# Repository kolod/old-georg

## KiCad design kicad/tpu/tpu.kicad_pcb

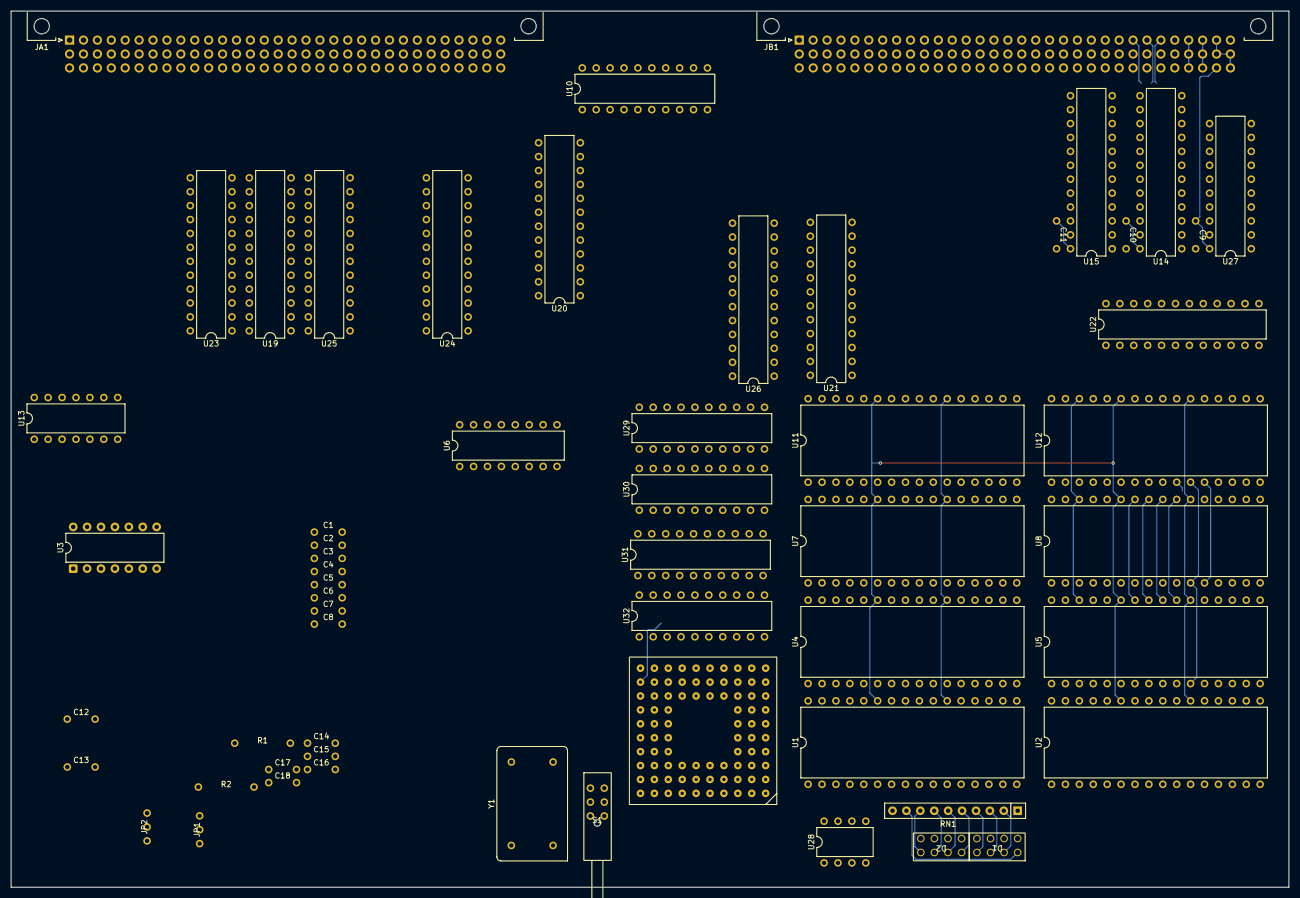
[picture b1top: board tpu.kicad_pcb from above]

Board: 4 copper layers, 233.4 x 160.0 mm, 58 parts (0 on the bottom side), 184 nets.

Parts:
C1, C2, C3, C4, C5, C6, C7, C8, C9, C10, C11, C12, C13, C14, C15, C16, C17, C18: 100nF; C104
D1, D2: 555-4001
JA1: 0903196X921
JB1: 0903196X921
JP1, JP2: Jumper
R1, R2: 100; R101
RN1: 1k; R_Array_SIP10
S1: 1840.6131
U1, U2, U4, U5, U7, U8, U11, U12: V62C5181024LL-70P; DIP-32_W15.24mm-tight
U3: 74F32; DIP-14_W7.62mm
U6: 74LS123; DIP-16_W7.62mm-tight
U10: 74F240; DIP-20_W7.62mm-tight
U13: 74S37; DIP-14_W7.62mm-tight
U14, U15: 74F842; DIP-24_W7.62mm-tight
U16: 84pin grid array
U19, U20, U21, U22, U23, U24, U25, U26: PALCE20V8H-15PC/4; DIP-24_W7.62mm-tight
U27: 74F640; DIP-20_W7.62mm-tight
U28: MAX690xPA; DIP-8_W7.62mm-tight
U29, U30, U31, U32: 74F573; DIP-20_W7.62mm-tight
Y1: IQXO-350C; Oscillator_DIP-14-tight

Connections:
+5V: C1.1, C2.1, C3.1, C4.1, C5.1, C6.1, C7.1, C8.1, C9.1, C10.1, C11.1, C12.1, C13.1, C14.1, C15.1, C16.1, JA1.a1, JA1.a2, JA1.b1, JA1.b2, JA1.c1, JA1.c2, JB1.a31, JB1.a32, JB1.b31, JB1.b32, JB1.c31, JB1.c32, JP1.3 (B), RN1.1 (R1), U1.30 (CS2/CE2), U1.32 (VCC), U2.30 (CS2/CE2), U2.32 (VCC), U3.14 (VCC), U4.30 (CS2/CE2), U4.32 (VCC), U5.30 (CS2/CE2), U5.32 (VCC), U6.9 (A), U6.16 (VCC), U7.30 (CS2/CE2), U7.32 (VCC), U8.30 (CS2/CE2), U8.32 (VCC), U10.20 (VCC), U11.30 (CS2/CE2), U11.32 (VCC), U12.30 (CS2/CE2), U12.32 (VCC), U13.1, U13.4, U13.14 (VCC), U14.24 (VCC), U15.24 (VCC), U16.A2 (Link_Special), U16.C2 (VDD), U16.C5 (VDD), U16.E2 (Boot_from_ROM), U16.E10 (VDD), U16.H4 (VDD), U19.24 (VCC), U20.24 (VCC), U21.24 (VCC), U22.24 (VCC), U23.24 (VCC), U24.24 (VCC), U25.24 (VCC), U26.24 (VCC), U27.20 (VCC), U28.2 (VCC), U29.20 (VCC), U30.20 (VCC), U31.20 (VCC), U32.20 (VCC), Y1.14 (Vcc)
/Multibus/ADR0: JB1.a24, U15.23 (Q0)
/Multibus/ADR1: JB1.b24, U15.22 (Q1)
/Multibus/ADR2: JB1.a23, U15.21 (Q2)
/Multibus/ADR3: JB1.b23, U15.20 (Q3)
/Multibus/ADR4: JB1.a22, U15.19 (Q4)
/Multibus/ADR5: JB1.b22, U15.18 (Q5)
/Multibus/ADR6: JB1.a21, U15.17 (Q6)
/Multibus/ADR7: JB1.b21, U15.16 (Q7)
/Multibus/ADR8: JB1.a20, U15.15 (Q8)
/Multibus/ADR9: JB1.b20, U15.14 (Q9)
/Multibus/ADR10: JB1.a19, U14.23 (Q0)
/Multibus/ADR11: JB1.b19, U14.22 (Q1)
/Multibus/ADR12: JB1.a18, U14.21 (Q2)
/Multibus/ADR13: JB1.b18, U14.20 (Q3)
/Multibus/ADR14: JB1.a17, U14.19 (Q4)
/Multibus/ADR15: JB1.b17, U14.18 (Q5)
/Multibus/ADR16: JB1.a16, U14.17 (Q6)
/Multibus/ADR17: JB1.b16, U14.16 (Q7)
/Multibus/ADR18: JB1.a15, U14.15 (Q8)
/Multibus/ADR19: JB1.b15, U14.14 (Q9)
/Multibus/DAT0: JB1.a28, U27.18 (B0)
/Multibus/DAT1: JB1.b28, U27.17 (B1)
/Multibus/DAT2: JB1.a27, U27.16 (B2)
/Multibus/DAT3: JB1.b27 (b26), U27.15 (B3)
/Multibus/DAT4: JB1.a26, U27.14 (B4)
/Multibus/DAT5: JB1.b26, U27.13 (B5)
/Multibus/DAT6: JB1.a25, U27.12 (B6)
/Multibus/DAT7: JB1.b25, U27.11 (B7)
/RAM/D0: U1.13 (I/O0), U2.13 (I/O0)
/RAM/D1: U1.14 (I/O1), U2.14 (I/O1)
/RAM/D2: U1.15 (I/O2), U2.15 (I/O2)
/RAM/D3: U1.17 (I/O3), U2.17 (I/O3)
/RAM/D4: U1.18 (I/O4), U2.18 (I/O4)
/RAM/D5: U1.19 (I/O5), U2.19 (I/O5)
/RAM/D6: U1.20 (I/O6), U2.20 (I/O6)
/RAM/D7: U1.21 (I/O7), U2.21 (I/O7)
/RAM/D8: U4.13 (I/O0), U5.13 (I/O0)
/RAM/D9: U4.14 (I/O1), U5.14 (I/O1)
/RAM/D10: U4.15 (I/O2), U5.15 (I/O2)
/RAM/D11: U4.17 (I/O3), U5.17 (I/O3)
/RAM/D12: U4.18 (I/O4), U5.18 (I/O4)
/RAM/D13: U4.19 (I/O5), U5.19 (I/O5)
/RAM/D14: U4.20 (I/O6), U5.20 (I/O6)
/RAM/D15: U4.21 (I/O7), U5.21 (I/O7)
/RAM/D16: U7.13 (I/O0), U8.13 (I/O0)
/RAM/D17: U7.14 (I/O1), U8.14 (I/O1)
/RAM/D18: U7.15 (I/O2), U8.15 (I/O2)
/RAM/D19: U7.17 (I/O3), U8.17 (I/O3)
/RAM/D20: U7.18 (I/O4), U8.18 (I/O4)
/RAM/D21: U7.19 (I/O5), U8.19 (I/O5)
/RAM/D22: U7.20 (I/O6), U8.20 (I/O6)
/RAM/D23: U7.21 (I/O7), U8.21 (I/O7)
/RAM/D24: U11.13 (I/O0), U12.13 (I/O0)
/RAM/D25: U11.14 (I/O1), U12.14 (I/O1)
/RAM/D26: U11.15 (I/O2), U12.15 (I/O2)
/RAM/D27: U11.17 (I/O3), U12.17 (I/O3)
/RAM/D28: U11.18 (I/O4), U12.18 (I/O4)
/RAM/D29: U11.19 (I/O5), U12.19 (I/O5)
/RAM/D30: U11.20 (I/O6), U12.20 (I/O6)
/RAM/D31: U11.21 (I/O7), U12.21 (I/O7)
/RAM_SIZE: JP1.2 (C), U23.18 (I/O3)
/~RESET: S1.2, U28.7 (~RESET)
A0: U1.12 (A0), U2.12 (A0), U4.12 (A0), U5.12 (A0), U7.12 (A0), U8.12 (A0), U11.12 (A0), U12.12 (A0), U15.2 (D0), U19.2 (I1), U29.19 (Q0)
A1: U1.11 (A1), U2.11 (A1), U4.11 (A1), U5.11 (A1), U7.11 (A1), U8.11 (A1), U11.11 (A1), U12.11 (A1), U15.3 (D1), U19.3 (I2), U29.18 (Q1)
A2: U1.10 (A2), U2.10 (A2), U4.10 (A2), U5.10 (A2), U7.10 (A2), U8.10 (A2), U11.10 (A2), U12.10 (A2), U15.4 (D2), U19.4 (I3), U29.17 (Q2)
A3: U1.9 (A3), U2.9 (A3), U4.9 (A3), U5.9 (A3), U7.9 (A3), U8.9 (A3), U11.9 (A3), U12.9 (A3), U15.5 (D3), U19.23 (I13), U29.16 (Q3)
A4: U1.8 (A4), U2.8 (A4), U4.8 (A4), U5.8 (A4), U7.8 (A4), U8.8 (A4), U11.8 (A4), U12.8 (A4), U15.6 (D4), U29.15 (Q4)
A5: U1.7 (A5), U2.7 (A5), U4.7 (A5), U5.7 (A5), U7.7 (A5), U8.7 (A5), U11.7 (A5), U12.7 (A5), U15.7 (D5), U29.14 (Q5)
A6: U1.6 (A6), U2.6 (A6), U4.6 (A6), U5.6 (A6), U7.6 (A6), U8.6 (A6), U11.6 (A6), U12.6 (A6), U15.8 (D6), U29.13 (Q6)
A7: U1.5 (A7), U2.5 (A7), U4.5 (A7), U5.5 (A7), U7.5 (A7), U8.5 (A7), U11.5 (A7), U12.5 (A7), U15.9 (D7), U29.12 (Q7)
A8: U1.27 (A8), U2.27 (A8), U4.27 (A8), U5.27 (A8), U7.27 (A8), U8.27 (A8), U11.27 (A8), U12.27 (A8), U15.10 (D8), U30.12 (Q7)
A9: U1.26 (A9), U2.26 (A9), U4.26 (A9), U5.26 (A9), U7.26 (A9), U8.26 (A9), U11.26 (A9), U12.26 (A9), U15.11 (D9), U30.13 (Q6)
A10: U1.23 (A10), U2.23 (A10), U4.23 (A10), U5.23 (A10), U7.23 (A10), U8.23 (A10), U11.23 (A10), U12.23 (A10), U14.2 (D0), U30.14 (Q5)
A11: U1.25 (A11), U2.25 (A11), U4.25 (A11), U5.25 (A11), U7.25 (A11), U8.25 (A11), U11.25 (A11), U12.25 (A11), U14.3 (D1), U30.15 (Q4)
A12: U1.4 (A12), U2.4 (A12), U4.4 (A12), U5.4 (A12), U7.4 (A12), U8.4 (A12), U11.4 (A12), U12.4 (A12), U14.4 (D2), U30.16 (Q3)
A13: U1.28 (A13), U2.28 (A13), U4.28 (A13), U5.28 (A13), U7.28 (A13), U8.28 (A13), U11.28 (A13), U12.28 (A13), U14.5 (D3), U30.17 (Q2)
A14: U1.3 (A14), U2.3 (A14), U4.3 (A14), U5.3 (A14), U7.3 (A14), U8.3 (A14), U11.3 (A14), U12.3 (A14), U14.6 (D4), U30.18 (Q1)
A15: U1.31 (A15), U2.31 (A15), U4.31 (A15), U5.31 (A15), U7.31 (A15), U8.31 (A15), U11.31 (A15), U12.31 (A15), U14.7 (D5), U30.19 (Q0)
A16: U1.2 (A16), U2.2 (A16), U4.2 (A16), U5.2 (A16), U7.2 (A16), U8.2 (A16), U11.2 (A16), U12.2 (A16), U14.8 (D6), U31.19 (Q0)
A17: U14.9 (D7), U31.18 (Q1)
A18: U14.10 (D8), U31.17 (Q2)
A19: U14.11 (D9), U31.16 (Q3)
AD2: U16.J10 (AD2), U27.4 (A2), U29.2 (D0)
AD3: U16.H9 (AD3), U27.5 (A3), U29.3 (D1)
AD4: U16.H8 (AD4), U27.6 (A4), U29.4 (D2)
AD5: U16.J9 (AD5), U27.7 (A5), U29.5 (D3)
AD6: U16.J8 (AD6), U27.8 (A6), U29.6 (D4)
AD7: U16.K10 (AD7), U27.9 (A7), U29.7 (D5)
AD8: U16.H7 (AD8), U29.8 (D6)
AD9: U16.K9 (AD9), U29.9 (D7)
AD10: U16.K8 (AD10), U30.9 (D7)
AD11: U16.K7 (AD11), U30.8 (D6)
AD12: U16.H6 (AD12), U30.7 (D5)
AD13: U16.J6 (AD13), U30.6 (D4)
AD14: U16.K6 (AD14), U30.5 (D3)
AD15: U16.K5 (AD15), U30.4 (D2)
AD16: U16.H5 (AD16), U30.3 (D1)
AD17: U16.J5 (AD17), U30.2 (D0)
AD18: U16.K4 (AD18), U31.2 (D0)
AD19: U16.J4 (AD19), U31.3 (D1)
AD20: U16.K3 (AD20), U31.4 (D2)
AD21: U16.K2 (AD21), U31.5 (D3)
AD22: U16.J3 (AD22), U31.6 (D4)
AD23: U16.H3 (AD23), U31.7 (D5)
AD24: U16.J2 (AD24), U31.8 (D6)
AD25: U16.H2 (AD25), U31.9 (D7)
AD26: U16.K1 (AD26), U32.9 (D7)
AD27: U16.G3 (AD27), U32.8 (D6)
AD28: U16.J1 (AD28), U32.7 (D5)
AD29: U16.H1 (AD29), U32.6 (D4)
AD30: U16.G1 (AD30), U32.5 (D3)
AD31: U16.F3 (AD31), U32.4 (D2)
Analyse: JA1.b25, U16.F2 (Analyse)
BCLK: U13.6, U21.1 (CLK/I0)
BUS_DIR: U25.20 (I/O5), U27.1 (T/R)
BUS_LE: U14.13 (LE), U15.13 (LE), U22.16 (I/O1)
CLK10: JB1.c1, U13.3
DM: C1.2, C2.2, C3.2, C4.2, C5.2, C6.2, C7.2, C8.2, C9.2, C10.2, C11.2, C12.2, C13.2, C14.2, C15.2, C16.2, JA1.a3, JA1.a4, JA1.b3, JA1.b4, JA1.c3, JA1.c4, JB1.a29, JB1.a30, JB1.b29, JB1.b30, JB1.c29, JB1.c30, JP1.1 (A), S1.3, U1.16 (GND), U2.16 (GND), U3.7 (GND), U4.16 (GND), U5.16 (GND), U6.8 (GND), U7.16 (GND), U8.16 (GND), U10.10 (GND), U11.16 (GND), U12.16 (GND), U13.7 (GND), U16.A4 (Link_123_Special), U16.A9 (GND), U16.B1 (Proc_Speed_Select_0), U16.B4 (Link_0_Special), U16.B8 (Event_Req), U16.B9 (Mem_Req), U16.C1 (GND), U16.D2 (Proc_Speed_Select_2), U16.D3 (Error_In), U16.E1 (Disable_Int_RAM), U16.F1 (Proc_Speed_Select_1), U16.G2 (GND), U16.G9 (GND), U16.J7 (GND), U19.12 (GND), U20.12 (GND), U21.12 (GND), U22.12 (GND), U22.13 (OE/I11), U23.12 (GND), U24.12 (GND), U25.12 (GND), U25.13 (OE/I11), U26.12 (GND), U27.10 (GND), U28.3 (GND), U29.1 (OE), U29.10 (GND), U30.1 (OE), U30.10 (GND), U31.1 (OE), U31.10 (GND), U32.1 (OE), U32.10 (GND), Y1.7 (GND)
IORC: U10.4 (I1a), U25.17 (I/O2)
IOWC: U10.2 (I0a), U25.18 (I/O3)
MRDC: U10.8 (I3a), U25.15 (I/O0)
MWRC: U10.6 (I2a), U25.16 (I/O1)
unnamed: JP2.1 (A), U3.8
unnamed: JP2.3 (B), U3.11
unnamed: R1.1, R2.1
unnamed: D1.4, RN1.2 (R1.2)
unnamed: D1.6, RN1.3 (R2.2)
unnamed: D1.8, RN1.4 (R3.2)
unnamed: D2.2, RN1.5 (R4.2)
unnamed: D2.4, RN1.6 (R5.2)
unnamed: D2.6, RN1.7 (R6.2)
unnamed: D2.8, RN1.8 (R7.2)
unnamed: D1.2, RN1.9 (R8.2)
unnamed: U6.10 (B), U10.1 (OEa), U22.18 (I/O3), U25.2 (I1)
unnamed: C17.2, C18.2, U16.C3 (Cap_Minus)
unnamed: C17.1, C18.1, U16.C4 (Cap_Plus)
unnamed: U16.D8 (Mem_Rf), U26.20 (I/O5)
unnamed: U13.2, Y1.8 (OUT)
unnamed: D1.1, U19.15 (I/O0)
unnamed: D1.3, U19.16 (I/O1)
unnamed: D1.5, U19.17 (I/O2)
unnamed: D1.7, U19.18 (I/O3)
unnamed: D2.1, U19.19 (I/O4)
unnamed: D2.3, U19.20 (I/O5)
unnamed: D2.5, U19.21 (I/O6)
unnamed: D2.7, U19.22 (I/O7)
unnamed: U21.3 (I2), U22.3 (I2), U24.21 (I/O6), U25.3 (I2)
unnamed: U21.8 (I7), U22.11 (I10)
unnamed: U21.9 (I8), U22.7 (I6)
unnamed: U21.17 (I/O2), U22.5 (I4)
unnamed: U22.8 (I7), U25.5 (I4)
unnamed: U22.10 (I9), U25.6 (I5)
unnamed: U3.10, U23.14 (I12)
unnamed: U3.5, U23.22 (I/O7)
unnamed: U24.1 (CLK/I0), U26.14 (I12)
unnamed: U28.4 (PFI), U28.5 (~PFO)
PCLK: U16.A3 (Proc_Clock_Out), U22.1 (CLK/I0), U25.1 (CLK/I0), U26.1 (CLK/I0)
RESET: U16.E3 (Reset), U21.2 (I1), U22.2 (I1), U24.11 (I10), U25.19 (I/O4)
RESET_FROM_PC: JA1.b26, U25.7 (I6)
RfD1: U16.H10 (RfD1), U27.3 (A1)
TPU_CLK: R1.2, U16.B2 (Clock_In)
VBAT: JA1.a9, U28.8 (VBATT)
WrD0: U16.G8 (WrD0), U27.2 (A0)
~ALE: U3.9, U3.13, U16.E9 (MemS0), U21.4 (I3), U22.4 (I3), U29.11 (Load), U30.11 (Load), U31.11 (Load), U32.11 (Load)
~BCLK: JB1.a1, U13.5
~BPRN: JB1.c5, U21.5 (I4)
~BREQ: JB1.c7, U21.22 (I/O7)
~BUSY: JB1.a3, U21.18 (I/O3), U21.19 (I/O4)
~BUS_OE: U14.1 (OE), U15.1 (OE), U26.18 (I/O3), U27.19 (OE)
~CBRQ: JB1.a12, U21.20 (I/O5), U21.21 (I/O6)
~INIT: JB1.a2, U25.21 (I/O6)
~IORC: JB1.a6, U10.16 (O1a)
~IOWC: JB1.a7, U10.18 (O0a)
~MCE0: U1.22 (~CS1/~CE1), U3.6, U4.22 (~CS1/~CE1), U7.22 (~CS1/~CE1), U11.22 (~CS1/~CE1)
~MCE1: JP2.2 (C), U2.22 (~CS1/~CE1), U5.22 (~CS1/~CE1), U8.22 (~CS1/~CE1), U12.22 (~CS1/~CE1)
~MOE: U1.24 (~OE), U2.24 (~OE), U4.24 (~OE), U5.24 (~OE), U7.24 (~OE), U8.24 (~OE), U11.24 (~OE), U12.24 (~OE), U16.E8 (Mem_Rd)
~MRDC: JB1.a4, U10.12 (O3a)
~MWRC: JB1.a5, U10.14 (O2a)
~WB0: U1.29 (~WE), U2.29 (~WE), U16.D10 (MemWrB0), U19.1 (CLK/I0)
~WB1: U4.29 (~WE), U5.29 (~WE), U16.C10 (MemWrB1)
~WB2: U7.29 (~WE), U8.29 (~WE), U16.D9 (MemWrB2)
~WB3: U11.29 (~WE), U12.29 (~WE), U16.B10 (MemWrB3)
~XACK: JB1.a8, U21.6 (I5), U22.6 (I5)

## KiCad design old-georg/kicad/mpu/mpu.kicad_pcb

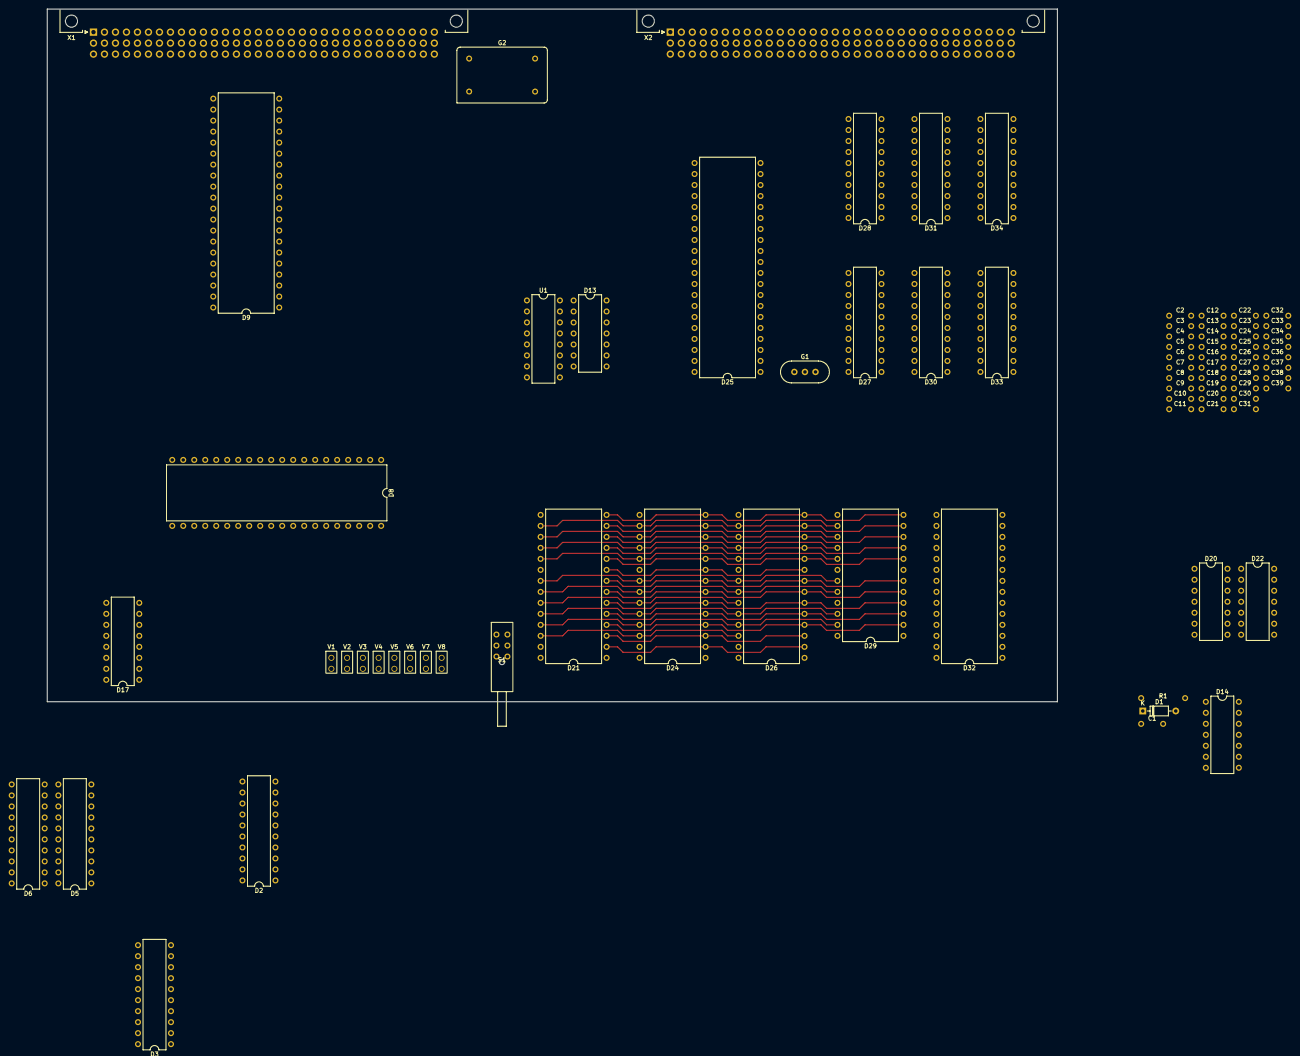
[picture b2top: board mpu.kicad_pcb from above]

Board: 2 copper layers, 233.4 x 160.0 mm, 78 parts (0 on the bottom side), 155 nets.

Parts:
C1: 33µF; C_5.08mm
C2, C3, C4, C5, C6, C7, C8, C9, C10, C11, C12, C13, C14, C15, C16, C17, C18, C19, C20, C21, C22, C23, C24, C25, C26, C27, C28, C29, C30, C31, C32, C33, C34, C35, C36, C37, C38, C39: 100nF; C_5.08mm
D1: 1N4448; D_DO-35_SOD27_P7.62mm_Horizontal
D2, D3, D5, D6, D30: 74LS245; DIP-20_W7.62mm-tight
D8: 8256; DIP-40_W15.24mm-tight
D9: 8255A; DIP-40_W15.24mm-tight
D13: 7414; DIP-14_W7.62mm-tight
D14: 7432; DIP-14_W7.62mm-tight
D17: 74LS138; DIP-16_W7.62mm-tight
D20: 7408; DIP-14_W7.62mm-tight
D21, D24, D26: D2764(128); DIP-28_W15.24mm-tight
D22: 7400; DIP-14_W7.62mm-tight
D25: 8085A; DIP-40_W15.24mm-tight
D27: 74LS373; DIP-20_W7.62mm-tight
D28, D31, D34: 8287; DIP-20_W7.62mm-tight
D29: D446; DIP-24_W15.24mm-tight
D32: 8259; DIP-28_W15.24mm-tight
D33: 74LS240; DIP-20_W7.62mm-tight
G1: HC-49; Crystal_HC49-U-3Pin_Vertical
G2: IQXO-350C; Oscillator_DIP-14-tight
R1: 10k; R_10.16mm
S1: 1840.6131
U1: 74LS175; DIP-16_W7.62mm-tight
V1, V2, V3, V4, V5, V6, V7, V8: 555-2x01
X1, X2: 0903196X921

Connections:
+5V: C2.1, C3.1, C4.1, C5.1, C6.1, C7.1, C8.1, C9.1, C10.1, C11.1, C12.1, C13.1, C14.1, C15.1, C16.1, C17.1, C18.1, C19.1, C20.1, C21.1, C22.1, C23.1, C24.1, C25.1, C26.1, C27.1, C28.1, C29.1, C30.1, C31.1, C32.1, C33.1, C34.1, C35.1, C36.1, C37.1, C38.1, C39.1, D1.1 (K), D2.20 (VCC), D3.20 (VCC), D5.20 (VCC), D6.20 (VCC), D8.40 (VCC), D9.26 (VCC), D13.14 (VCC), D14.14 (VCC), D17.16 (VCC), D20.1, D20.13, D21.1 (VPP), D21.27 (~PGM), D21.28 (VCC), D24.1 (VPP), D24.27 (~PGM), D24.28 (VCC), D25.5 (SID), D25.40 (VCC), D26.1 (VPP), D26.27 (~PGM), D26.28 (VCC), D27.20 (VCC), D28.11 (A->B), D28.20 (VCC), D29.24 (VCC), D30.20 (VCC), D31.11 (A->B), D31.20 (VCC), D32.16 (~SP/~EN), D32.28 (VCC), D33.20 (VCC), D34.20 (VCC), G2.14 (Vcc), R1.2, U1.16 (VCC), V1.2, V2.2, V3.2, V4.2, V5.2, V6.2, V7.2, V8.2, X1.a1, X1.a2, X1.b1, X1.b2, X1.c1, X1.c2, X2.a31, X2.a32, X2.b31, X2.b32, X2.c31, X2.c32
/Parallel Input-Output/PTA0: D6.2 (A0), D9.4 (PA0)
/Parallel Input-Output/PTA1: D6.3 (A1), D9.3 (PA1)
/Parallel Input-Output/PTA2: D6.4 (A2), D9.2 (PA2)
/Parallel Input-Output/PTA3: D6.5 (A3), D9.1 (PA3)
/Parallel Input-Output/PTA4: D6.6 (A4), D9.40 (PA4)
/Parallel Input-Output/PTA5: D6.7 (A5), D9.39 (PA5)
/Parallel Input-Output/PTA6: D6.8 (A6), D9.38 (PA6)
/Parallel Input-Output/PTA7: D6.9 (A7), D9.37 (PA7)
/Parallel Input-Output/PTB0: D3.2 (A0), D9.18 (PB0)
/Parallel Input-Output/PTB1: D3.3 (A1), D9.19 (PB1)
/Parallel Input-Output/PTB2: D3.4 (A2), D9.20 (PB2)
/Parallel Input-Output/PTB3: D3.5 (A3), D9.21 (PB3)
/Parallel Input-Output/PTB4: D3.6 (A4), D9.22 (PB4)
/Parallel Input-Output/PTB5: D3.7 (A5), D9.23 (PB5)
/Parallel Input-Output/PTB6: D3.8 (A6), D9.24 (PB6)
/Parallel Input-Output/PTB7: D3.9 (A7), D9.25 (PB7)
/Parallel Input-Output/PTC0: D5.2 (A0), D9.14 (PC0)
/Parallel Input-Output/PTC1: D5.3 (A1), D9.15 (PC1)
/Parallel Input-Output/PTC2: D5.4 (A2), D9.16 (PC2)
/Parallel Input-Output/PTC3: D5.5 (A3), D9.17 (PC3)
/Parallel Input-Output/PTC4: D2.2 (A0), D9.13 (PC4)
/Parallel Input-Output/PTC5: D2.3 (A1), D9.12 (PC5)
/Parallel Input-Output/PTC6: D2.4 (A2), D9.11 (PC6)
/Parallel Input-Output/PTC7: D2.5 (A3), D9.10 (PC7)
/μP,PROM,RAM/AD0: D25.12 (AD0), D27.3 (D0), D30.2 (A0)
/μP,PROM,RAM/AD1: D25.13 (AD1), D27.4 (D1), D30.3 (A1)
/μP,PROM,RAM/AD2: D25.14 (AD2), D27.7 (D2), D30.4 (A2)
/μP,PROM,RAM/AD3: D25.15 (AD3), D27.8 (D3), D30.5 (A3)
/μP,PROM,RAM/AD4: D25.16 (AD4), D27.13 (D4), D30.6 (A4)
/μP,PROM,RAM/AD5: D25.17 (AD5), D27.14 (D5), D30.7 (A5)
/μP,PROM,RAM/AD6: D25.18 (AD6), D27.17 (D6), D30.8 (A6)
/μP,PROM,RAM/AD7: D25.19 (AD7), D27.18 (D7), D30.9 (A7)
A0: D9.9 (A0), D21.10 (A0), D24.10 (A0), D26.10 (A0), D27.2 (O0), D29.8 (A0), D31.1 (A0), D32.27 (A0)
A1: D9.8 (A1), D21.9 (A1), D24.9 (A1), D26.9 (A1), D27.5 (O1), D29.7 (A1), D31.2 (A1)
A2: D14.1, D21.8 (A2), D24.8 (A2), D26.8 (A2), D27.6 (O2), D29.6 (A2), D31.3 (A2)
A3: D21.7 (A3), D24.7 (A3), D26.7 (A3), D27.9 (O3), D29.5 (A3), D31.4 (A3)
A4: D21.6 (A4), D24.6 (A4), D26.6 (A4), D27.12 (O4), D29.4 (A4), D31.5 (A4)
A5: D21.5 (A5), D24.5 (A5), D26.5 (A5), D27.15 (O5), D29.3 (A5), D31.6 (A5)
A6: D21.4 (A6), D24.4 (A6), D26.4 (A6), D27.16 (O6), D29.2 (A6), D31.7 (A6)
A7: D21.3 (A7), D24.3 (A7), D26.3 (A7), D27.19 (O7), D29.1 (A7), D31.8 (A7)
A8: D21.25 (A8), D24.25 (A8), D25.21 (A8), D26.25 (A8), D28.1 (A0), D29.23 (A8)
A9: D21.24 (A9), D24.24 (A9), D25.22 (A9), D26.24 (A9), D28.2 (A1), D29.22 (A9)
A10: D21.21 (A10), D24.21 (A10), D25.23 (A10), D26.21 (A10), D28.3 (A2), D29.19 (A10)
A11: D17.1 (A0), D21.23 (A11), D24.23 (A11), D25.24 (A11), D26.23 (A11), D28.4 (A3)
A12: D17.2 (A1), D21.2 (A12), D24.2 (A12), D25.25 (A12), D26.2 (A12), D28.5 (A4)
A13: D17.3 (A2), D21.26 (NC(A13)), D24.26 (NC(A13)), D25.26 (A13), D26.26 (NC(A13)), D28.6 (A5)
A14: D17.4 (E1), D25.27 (A14), D28.7 (A6)
A15: D17.5 (E2), D25.28 (A15), D28.8 (A7)
DIR A: D6.1 (A->B), U1.3 (~Q0)
DIR B: D3.1 (A->B), U1.6 (~Q1)
DIR C0: D5.1 (A->B), U1.11 (~Q2)
DIR C1: D2.1 (A->B), U1.14 (~Q3)
DT0: D8.1 (AD0), D9.34 (D0), D13.9, D21.11 (D0), D24.11 (D0), D26.11 (D0), D29.9 (D0), D30.18 (B0), D32.11 (D0), D34.1 (A0)
DT1: D8.2 (AD1), D9.33 (D1), D13.3, D21.12 (D1), D24.12 (D1), D26.12 (D1), D29.10 (D1), D30.17 (B1), D32.10 (D1), D34.2 (A1)
DT2: D8.3 (AD2), D9.32 (D2), D13.5, D21.13 (D2), D24.13 (D2), D26.13 (D2), D29.11 (D2), D30.16 (B2), D32.9 (D2), D34.3 (A2)
DT3: D8.4 (AD3), D9.31 (D3), D13.11, D21.15 (D3), D24.15 (D3), D26.15 (D3), D29.13 (D3), D30.15 (B3), D32.8 (D3), D34.4 (A3)
DT4: D8.5 (D4), D9.30 (D4), D21.16 (D4), D24.16 (D4), D26.16 (D4), D29.14 (D4), D30.14 (B4), D32.7 (D4), D34.5 (A4)
DT5: D8.6 (D5), D9.29 (D5), D21.17 (D5), D24.17 (D5), D26.17 (D5), D29.15 (D5), D30.13 (B5), D32.6 (D5), D34.6 (A5)
DT6: D8.7 (D6), D9.28 (D6), D21.18 (D6), D24.18 (D6), D26.18 (D6), D29.16 (D6), D30.12 (B6), D32.5 (D6), D34.7 (A6)
DT7: D8.8 (D7), D9.27 (D7), D21.19 (D7), D24.19 (D7), D26.19 (D7), D29.17 (D7), D30.11 (B7), D32.4 (D7), D34.8 (A7)
GND: C1.2, C2.2, C3.2, C4.2, C5.2, C6.2, C7.2, C8.2, C9.2, C10.2, C11.2, C12.2, C13.2, C14.2, C15.2, C16.2, C17.2, C18.2, C19.2, C20.2, C21.2, C22.2, C23.2, C24.2, C25.2, C26.2, C27.2, C28.2, C29.2, C30.2, C31.2, C32.2, C33.2, C34.2, C35.2, C36.2, C37.2, C38.2, C39.2, D2.10 (GND), D2.19 (CE), D3.10 (GND), D3.19 (CE), D5.10 (GND), D5.19 (CE), D6.10 (GND), D6.19 (CE), D8.16 (EXTINT), D8.20 (GND), D9.7 (GND), D13.7 (GND), D14.7 (GND), D17.8 (GND), D21.14 (GND), D24.14 (GND), D25.8 (RST6.5), D25.9 (RST5.5), D25.20 (GND), D25.39 (HOLD), D26.14 (GND), D27.1 (OE), D27.10 (GND), D28.10 (GND), D29.12 (GND), D30.10 (GND), D30.19 (CE), D31.10 (GND), D32.14 (GND), D33.1 (OEa), D33.10 (GND), D33.19 (OEb), D34.10 (GND), G1.2, G2.7 (GND), S1.2, U1.8 (GND), X1.a3, X1.a4, X1.a29, X1.a30, X1.b3, X1.b4, X1.b29, X1.b30, X1.c3, X1.c4, X1.c29, X1.c30, X2.a29, X2.a30, X2.b1, X2.b2, X2.b3, X2.b4, X2.b5, X2.b6, X2.b7, X2.b8, X2.b9, X2.b10, X2.b11, X2.b12, X2.b13, X2.b14, X2.b29, X2.b30, X2.c29, X2.c30
IO/~M: D17.6 (E3), D25.34 (IO/~M)
unnamed: C1.1, D1.2 (A), D13.1, R1.1, S1.3
unnamed: D9.6 (~CS), D14.3
unnamed: D17.11 (O4), D20.10
unnamed: D17.10 (O5), D20.9
unnamed: D22.6, D22.9
unnamed: D22.10, D22.13
unnamed: D25.1 (X1), G1.1
unnamed: D25.2 (X2), G1.3
unnamed: D22.3, D30.1 (A->B)
unnamed: D32.18 (IR0), D33.3 (O3b)
unnamed: D32.19 (IR1), D33.5 (O2b)
unnamed: D32.20 (IR2), D33.7 (O1b)
unnamed: D32.21 (IR3), D33.9 (O0b)
unnamed: D32.22 (IR4), D33.12 (O3a)
unnamed: D32.23 (IR5), D33.14 (O2a)
unnamed: D32.24 (IR6), D33.16 (O1a)
unnamed: D32.25 (IR7), D33.18 (O0a)
unnamed: D13.8, U1.4 (D0)
unnamed: D13.4, U1.5 (D1)
unnamed: D13.6, U1.12 (D2)
unnamed: D13.10, U1.13 (D3)
PA0: D6.18 (B0), X1.a10
PA1: D6.17 (B1), X1.a11
PA2: D6.16 (B2), X1.a12
PA3: D6.15 (B3), X1.a13
PA4: D6.14 (B4), X1.a14
PA5: D6.13 (B5), X1.a15
PA6: D6.12 (B6), X1.a16
PA7: D6.11 (B7), X1.a17
PB0: D3.18 (B0), X1.a19
PB1: D3.17 (B1), X1.a20
PB2: D3.16 (B2), X1.a21
PB3: D3.15 (B3), X1.a22
PB4: D3.14 (B4), X1.a23
PB5: D3.13 (B5), X1.a24
PB6: D3.12 (B6), X1.a25
PB7: D3.11 (B7), X1.a26
PC0: D5.18 (B0), X1.c10
PC1: D5.17 (B1), X1.c11
PC2: D5.16 (B2), X1.c12
PC3: D5.15 (B3), X1.c13
PC4: D2.18 (B0), X1.c14
PC5: D2.17 (B1), X1.c15
PC6: D2.16 (B2), X1.c16
PC7: D2.15 (B3), X1.c17
~ADDR0: D31.19 (B0), X2.a24
~ADDR1: D31.18 (B1), X2.b24
~ADDR2: D31.17 (B2), X2.a23
~ADDR3: D31.16 (B3), X2.b23
~ADDR4: D31.15 (B4), X2.a22
~ADDR5: D31.14 (B5), X2.b22
~ADDR6: D31.13 (B6), X2.a21
~ADDR7: D31.12 (B7), X2.b21
~ADDR8: D28.19 (B0), X2.a20
~ADDR9: D28.18 (B1), X2.b20
~ADDR10: D28.17 (B2), X2.a19
~ADDR11: D28.16 (B3), X2.b19
~ADDR12: D28.15 (B4), X2.a18
~ADDR13: D28.14 (B5), X2.b18
~ADDR14: D28.13 (B6), X2.a17
~ADDR15: D28.12 (B7), X2.b17
~ADEN: D28.9 (OE), D31.9 (OE), D34.9 (OE)
~ALE: D8.9 (ALE), D22.12
~DAT0: D34.19 (B0), X2.a28
~DAT1: D34.18 (B1), X2.b28
~DAT2: D34.17 (B2), X2.a27
~DAT3: D34.16 (B3), X2.b27 (b26)
~DAT4: D34.15 (B4), X2.a26
~DAT5: D34.14 (B5), X2.b26
~DAT6: D34.13 (B6), X2.a25
~DAT7: D34.12 (B7), X2.b25
~INT0: D33.2 (I0a), X2.c20
~INT1: D33.4 (I1a), X2.c19
~INT2: D33.6 (I2a), X2.c18
~INT3: D33.8 (I3a), X2.c17
~INT4: D33.11 (I0b), X2.c16
~INT5: D33.13 (I1b), X2.c15
~INT6: D33.15 (I2b), X2.c14
~INT7: D33.17 (I3b), X2.c13
~INTA1: D14.11, D32.26 (~INTA)
~INTA2: D8.14 (~INTA), D14.8
~INTA: D14.10, D14.13, D22.2, D25.11 (~INTA)
~INTR1: D14.5, D32.17 (INT)
~INTR2: D8.15 (INT), D14.4
~IOS4: D8.13 (~CS), D20.8
~IOS6: D17.9 (O6), D32.1 (~CS)
~IOS7: D14.2, D17.7 (O7)
~RDO: D20.2, D25.32 (~RD)
~RD: D8.10 (~RD), D9.5 (~RD), D20.3, D21.22 (~OE), D22.1, D24.22 (~OE), D26.22 (~OE), D29.20 (~OE), D32.3 (~RD)
~RESET: D8.12 (RESET), D25.36 (~RESI), U1.1 (~Mr)
~WRO: D20.12, D25.31 (~WR), D29.21 (~WE), D32.2 (~WR)
~WR: D8.11 (~WR), D9.36 (~WR), D20.11

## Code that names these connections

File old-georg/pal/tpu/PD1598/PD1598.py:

from machine import Pin
from time import sleep

POWER      = Pin(0, Pin.OUT)

BCLK       = Pin(1, Pin.OUT)
RESET      = Pin(2, Pin.OUT)
BUS_EN     = Pin(3, Pin.OUT)
ALE        = Pin(4, Pin.OUT)
BPRN       = Pin(5, Pin.OUT)
XACK       = Pin(6, Pin.OUT)
PD1604_15  = Pin(7, Pin.OUT)
PD1597_17  = Pin(8, Pin.OUT)
WRITE      = Pin(9, Pin.OUT)

X1         = Pin(10, Pin.OUT)
X2         = Pin(11, Pin.OUT)
X3         = Pin(13, Pin.OUT)

Y1         = Pin(14, Pin.IN, None)
Y2         = Pin(15, Pin.IN, None)
Y3         = Pin(16, Pin.IN, None)
PD1604_16  = Pin(17, Pin.IN, None)
BUSY1      = Pin(18, Pin.IN, None)
BUSY2      = Pin(19, Pin.IN, None)
CBRQ1      = Pin(20, Pin.IN, None)
CBRQ2      = Pin(21, Pin.IN, None)
BREQ       = Pin(22, Pin.IN, None)
Y4         = Pin(26, Pin.IN, None)

def gray_code_generator(bits):
    if bits <= 0:
        raise ValueError("Number of bits must be a positive integer.")

    n = 1 << bits  # Total number of Gray codes (2^bits)
    for i in range(n):
        yield i ^ (i >> 1)  # Generate Gray code by applying the formula


class PD1598:
    
    def __init__(self):
        self.pause = 0.005
        POWER.off()        
        
    def on(self):
        sleep(0.001)
        RESET.off()
        POWER.on()
        sleep(0.01)
        
    def off(self):
        POWER.off()
        sleep(0.1)
        
    def pulse(self):
        sleep(self.pause)
        BCLK.off()
        sleep(self.pause)
        BCLK.on()
        sleep(self.pause)
        
    def reset(self):
        RESET.on()
        self.pulse()        
        RESET.off()
        sleep(self.pause)
        
    def test(self):
        
        self.on()
        self.reset()        
        
        for x in gray_code_generator(10):
            BUS_EN.value(x & 0x0001)
            ALE.value(x & 0x0002)
            BPRN.value(x & 0x0004)
            XACK.value(x & 0x0008)
            PD1604_15.value(x & 0x0010)
            PD1597_17.value(x & 0x0020)
            WRITE.value(x & 0x0040)
            X1.value(x & 0x0080)
            X2.value(x & 0x0100)
            X3.value(x & 0x0200)
            self.pulse()
            
        self.off()
        
        
    def test_breq(self):
        self.on()
        
        for x in [X1, X2, X3, WRITE, RESET, ALE, PD1604_15, PD1597_17]:
           
            X1.off()
            X2.off()
            X3.off()
            WRITE.off()
            BCLK.on()
            RESET.off()
            ALE.on()
            BPRN.off()
            PD1604_15.on()
            PD1597_17.on()
            sleep(self.pause)
            self.pulse()
            
            x.toggle()
            sleep(self.pause)
            self.pulse()
        
        self.off()


pd = PD1598()
pd.test()
#pd.test_breq()

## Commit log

2025-04-25 initial release
2025-04-28 Add vfd
2025-04-29 Add CSV
2025-04-29 Add rom's
2025-10-06 add plc roms
2025-10-09 add plc-doc.md
2025-12-03 Move files to old-georg
2025-12-03 longitudinal-georg
2025-12-03 set crlf for *.dnl files
2025-12-03 add simoreg dc master manual
